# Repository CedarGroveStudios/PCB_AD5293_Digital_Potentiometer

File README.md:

# PCB_AD5293_Digital_Potentiometer
### _A small breakout board for the 100K AD5293 digital potentiometer._

The AD5293 Digital Potentiometer is an SPI, 100K-ohm device. The potentiometer sports 1024 resistance steps. The digital logic power requires 2.7v to 5.5v. The potentiometer circuit operates with dual analog supply voltages from +/-9v to +/-16.5v. The pins act similarly to a passive resistive potentiometer, but require that voltages placed on any of the three pins not exceed the analog power supply voltages.

The Cedar Grove AD5293 custom breakout board provides power and signal connections for SPI and the potentiometer chip. The AD5293 is also used in the AD9833-based Cedar Grove Precision VCO Eurorack module.

A CircuitPython library is available: https://github.com/CedarGroveStudios/CircuitPython_AD5293

<a href="https://oshpark.com/shared_projects/B8xvjFWI"></img></a>

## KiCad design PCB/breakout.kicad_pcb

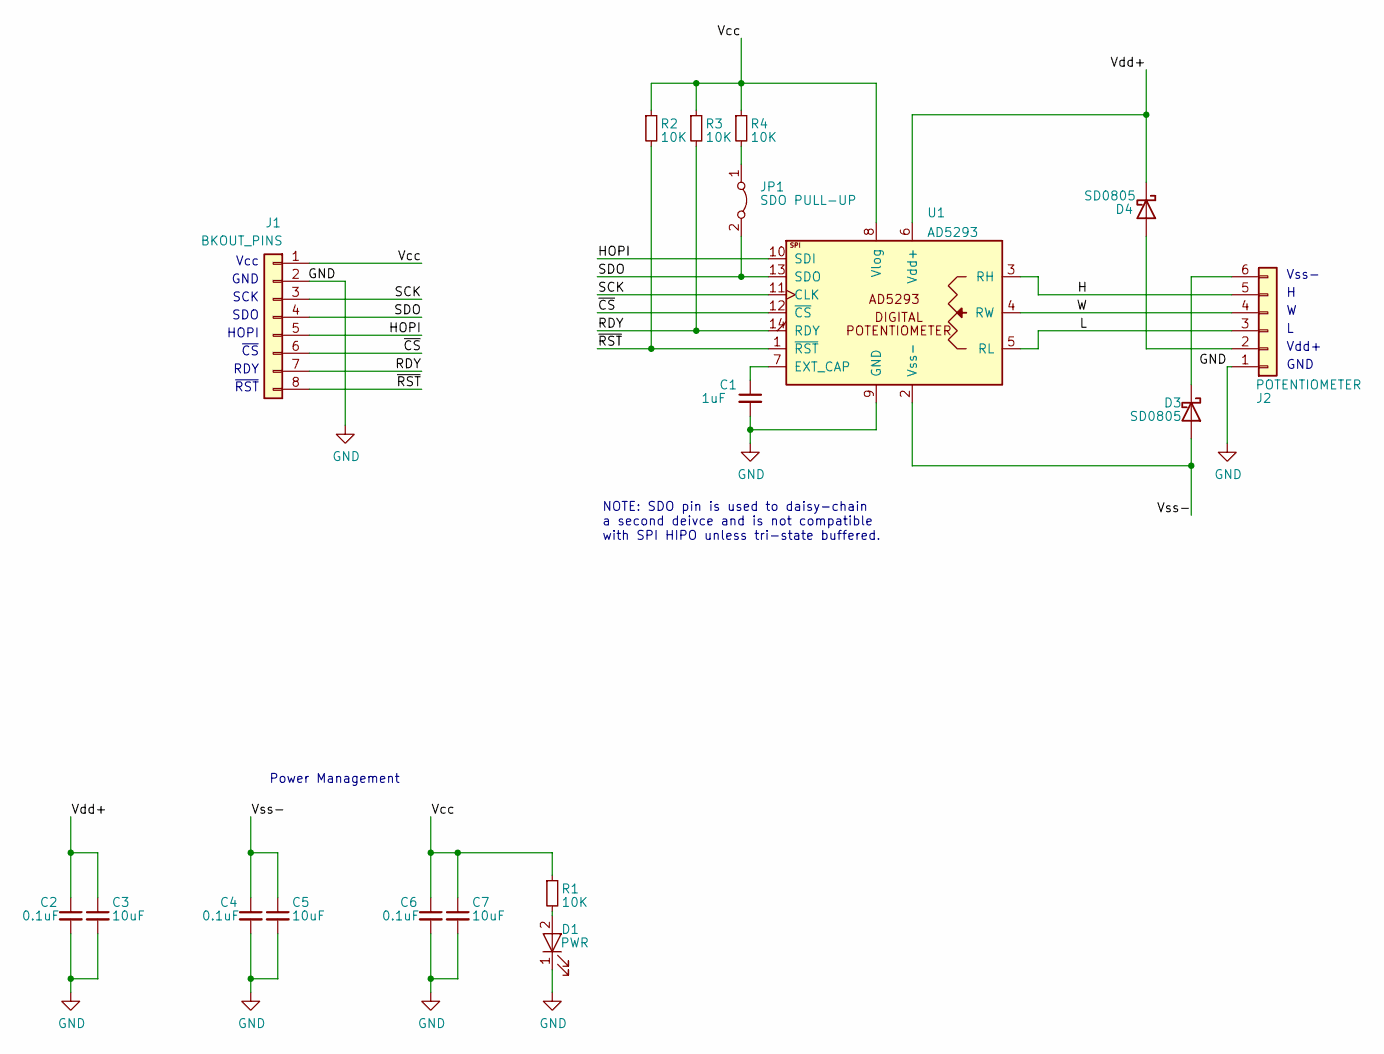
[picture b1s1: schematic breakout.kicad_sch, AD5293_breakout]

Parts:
C1: 1uF; C_0805_2012Metric
C2, C4, C6: 0.1uF; C_0805_2012Metric
C3, C5, C7: 10uF; C_0805_2012Metric
D1: PWR; LED_0805_2012Metric
D3, D4: SD0805; D_0805_2012Metric
J1: BKOUT_PINS; PinSocket_1x08_P2.54mm_Vertical
J2: POTENTIOMETER; PinSocket_1x06_P2.54mm_Vertical
JP1: SDO PULL-UP; SolderJumper-2_P1.3mm_Bridged_RoundedPad1.0x1.5mm
R1, R2, R3, R4: 10K; R_0805_2012Metric
U1: AD5293; TSSOP-14_4.4x5mm_P0.65mm

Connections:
/H: J2.5, U1.3 (RH)
/HOPI: J1.5, U1.10 (SDI)
/L: J2.3, U1.5 (RL)
/RDY: J1.7, R3.2, U1.14 (RDY)
/SCK: J1.3, U1.11 (CLK)
/SDO: J1.4, JP1.2 (B), U1.13 (SDO)
/Vcc: C6.1, C7.1, J1.1, R1.1, R2.1, R3.1, R4.1, U1.8 (Vlog)
/Vdd+: C2.1, C3.1, D4.1 (K), U1.6 (Vdd+)
/Vss-: C4.1, C5.1, D3.2 (A), U1.2 (Vss-)
/W: J2.4, U1.4 (RW)
/~CS: J1.6, U1.12 (~CS)
/~RST: J1.8, R2.2, U1.1 (~RST)
GND: C1.2, C2.2, C3.2, C4.2, C5.2, C6.2, C7.2, D1.1 (K), J1.2, J2.1, U1.9 (GND)
unnamed: C1.1, U1.7 (EXT_CAP)
unnamed: D1.2 (A), R1.2
unnamed: D3.1 (K), J2.6
unnamed: D4.2 (A), J2.2
unnamed: JP1.1 (A), R4.2

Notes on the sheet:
Vss-
Vcc
RDY
SCK
~{CS}
Vdd+
GND
Power Management
HOPI
~{RST}
SDO
NOTE: SDO pin is used to daisy-chain a second deivce and is not compatible with SPI HIPO unless tri-state buffered.

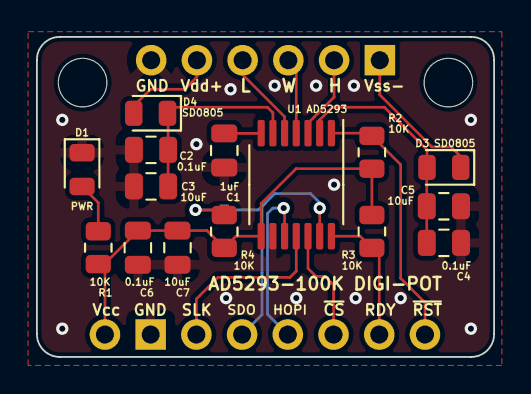
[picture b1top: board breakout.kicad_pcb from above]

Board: 2 copper layers, 25.4 x 17.8 mm, 18 parts (1 on the bottom side), 18 nets.

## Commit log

2023-02-05 initial repo load
2023-02-05 update backup
2023-02-05 create gerbers
2023-02-05 rev 0.0.0 final
2023-02-05 update gerbers
2023-02-06 add mounting holes
2023-02-06 add mounting holes; version 1.0.0
2023-02-06 update docs
2023-02-07 update backups
2023-02-08 refactor layout design; simplify routing
2023-02-08 update gerbers and backups
2023-03-19 kicad backup
2023-03-26 update PCB design
2023-03-27 update kicad backup
2023-04-21 update design; add SDO pull-up jumper
2023-04-21 update kicad backups
2023-04-21 update shared OSHPark link
2023-04-21 update jumper solder mask
